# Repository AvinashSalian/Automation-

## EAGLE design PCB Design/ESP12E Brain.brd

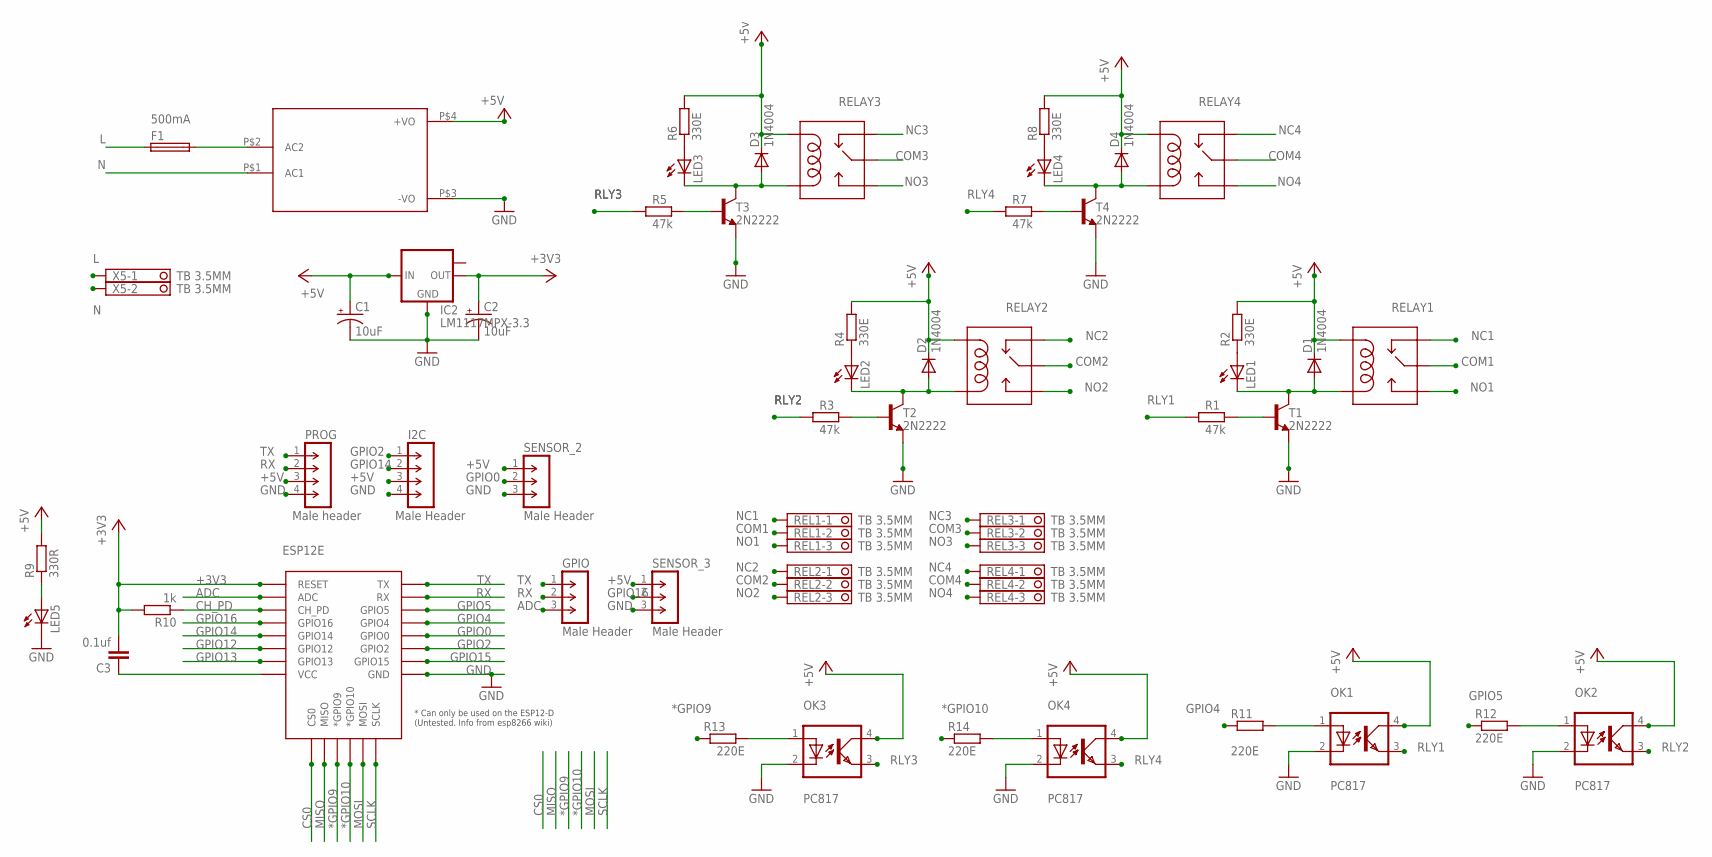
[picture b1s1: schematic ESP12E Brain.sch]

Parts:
C1, C2: 10uF; CPOL-RADIAL-2.5MM-5MM
C3: 0.1uf; C025-030X050
D1, D2, D3, D4: 1N4004; DO41-10
ESP12E: ESP12ESMD; ESP12E-SMD
F1: 500mA; FUSE_HOLDER_5X20MM
GPIO: Male Header; SIP-100-03-32
HLK: HLK-PM013W; HLK-PM01
I2C: Male Header; SIP-100-04-32
IC2: LM1117MPX-3.3; SOT223
LED1, LED2, LED3, LED4, LED5: LEDCHIP-LED0603; CHIP-LED0603
OK1, OK2, OK3, OK4: PC817; DIL04
PROG: Male header; SIP-100-04-32
R1, R3, R5, R7: 47k; 0204/7
R2, R4, R6, R8: 330E; 0204/7
R9: 330R; 0204/7
R10: 1k; 0204/7
R11, R12, R13, R14: 220E; 0204/7
REL1, REL2, REL3, REL4: TB 3.5MM; TERMINAL-BLOCK-3-PIN-3.5MM-ROUND-PAD
RELAY1, RELAY2, RELAY3, RELAY4: SRD-0XVDC-SL-CSRD-05VDC-SL-C; SRD-0XVDC-SL-C
SENSOR_2, SENSOR_3: Male Header; SIP-100-03-32
T1, T2, T3, T4: 2N2222; TO92-EBC-OVAL
X5: TB 3.5MM; TERMINAL-BLOCK-2-PIN-3.5MM-ROUND-PAD

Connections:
*GPIO9: ESP12E.GPIO9 (*GPIO9), R13.1
*GPIO10: ESP12E.GPIO10 (*GPIO10), R14.1
+3V3: C2.1 (+), C3.2, ESP12E.RESET, IC2.2 (OUT), R10.2
+5V: C1.1 (+), D1.C, D2.C, D3.C, D4.C, HLK.P$4 (+VO), I2C.3, IC2.3 (IN), OK1.4 (COL), OK2.4 (COL), OK3.4 (COL), OK4.4 (COL), PROG.3, R2.2, R4.2, R6.2, R8.2, R9.2, RELAY1.COIL1, RELAY2.COIL1, RELAY3.COIL1, RELAY4.COIL1, SENSOR_2.1, SENSOR_3.1
AC2: F1.2, HLK.P$2 (AC2)
ADC: ESP12E.ADC, GPIO.3
CH_PD: ESP12E.CH_PD, R10.1
COM1: REL1.2, RELAY1.SWCOMMON
COM2: REL2.2, RELAY2.SWCOMMON
COM3: REL3.2, RELAY3.SWCOMMON
COM4: REL4.2, RELAY4.SWCOMMON
CS0: ESP12E.CS0
GND: C1.2 (-), C2.2 (-), ESP12E.GND, HLK.P$3 (-VO), I2C.4, IC2.1 (GND), LED5.C, OK1.2 (C), OK2.2 (C), OK3.2 (C), OK4.2 (C), PROG.4, SENSOR_2.3, SENSOR_3.3, T1.E, T2.E, T3.E, T4.E
GPIO0: ESP12E.GPIO0, SENSOR_2.2
GPIO2: ESP12E.GPIO2, I2C.1
GPIO4: ESP12E.GPIO4, R11.1
GPIO5: ESP12E.GPIO5, R12.1
GPIO12: ESP12E.GPIO12
GPIO13: ESP12E.GPIO13
GPIO14: ESP12E.GPIO14, I2C.2
GPIO15: ESP12E.GPIO15
GPIO16: ESP12E.GPIO16, SENSOR_3.2
L: F1.1, X5.1
MISO: ESP12E.MISO
MOSI: ESP12E.MOSI
N: HLK.P$1 (AC1), X5.2
unnamed: R1.2, T1.B
unnamed: D1.A, LED1.C, RELAY1.COIL0, T1.C
unnamed: OK1.1 (A), R11.2
unnamed: D2.A, LED2.C, RELAY2.COIL0, T2.C
unnamed: LED1.A, R2.1
unnamed: R3.2, T2.B
unnamed: LED2.A, R4.1
unnamed: D3.A, LED3.C, RELAY3.COIL0, T3.C
unnamed: OK2.1 (A), R12.2
unnamed: R5.2, T3.B
unnamed: LED3.A, R6.1
unnamed: D4.A, LED4.C, RELAY4.COIL0, T4.C
unnamed: OK3.1 (A), R13.2
unnamed: R7.2, T4.B
unnamed: LED4.A, R8.1
unnamed: C3.1, ESP12E.VCC
unnamed: LED5.A, R9.1
unnamed: OK4.1 (A), R14.2
NC1: REL1.1, RELAY1.SWCLOSED (SWCLOSE)
NC2: REL2.1, RELAY2.SWCLOSED (SWCLOSE)
NC3: REL3.1, RELAY3.SWCLOSED (SWCLOSE)
NC4: REL4.1, RELAY4.SWCLOSED (SWCLOSE)
NO1: REL1.3, RELAY1.SWOPEN
NO2: REL2.3, RELAY2.SWOPEN
NO3: REL3.3, RELAY3.SWOPEN
NO4: REL4.3, RELAY4.SWOPEN
RLY1: OK1.3 (EMIT), R1.1
RLY2: OK2.3 (EMIT), R3.1
RLY3: OK3.3 (EMIT), R5.1
RLY4: OK4.3 (EMIT), R7.1
RX: ESP12E.RXD0 (RX), GPIO.2, PROG.2
SCLK: ESP12E.SCLK
TX: ESP12E.TXD0 (TX), GPIO.1, PROG.1

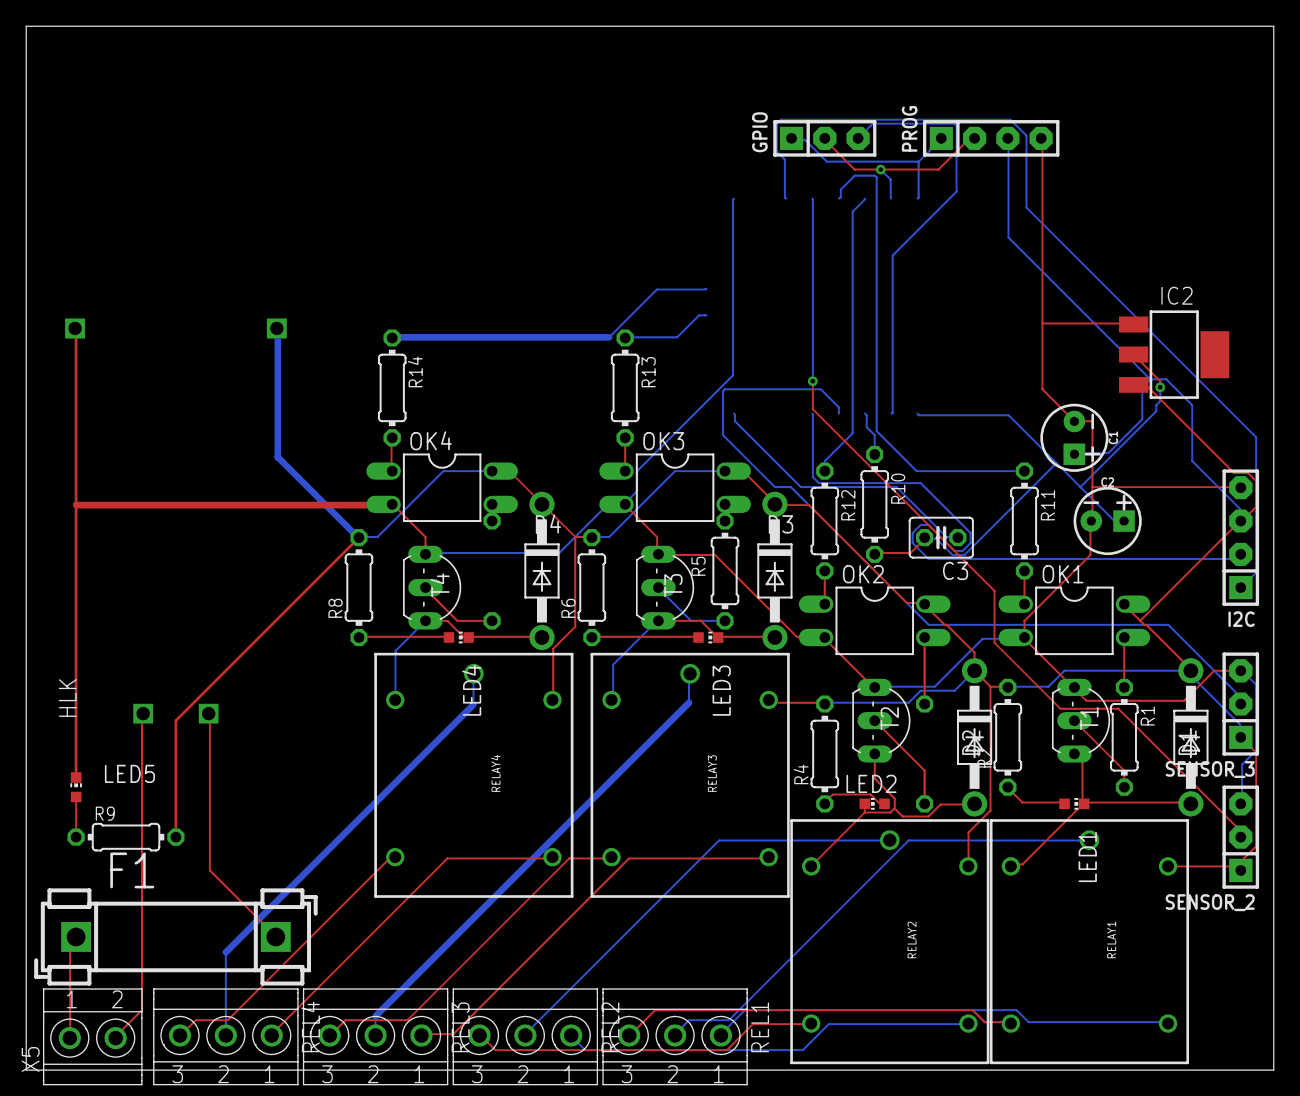
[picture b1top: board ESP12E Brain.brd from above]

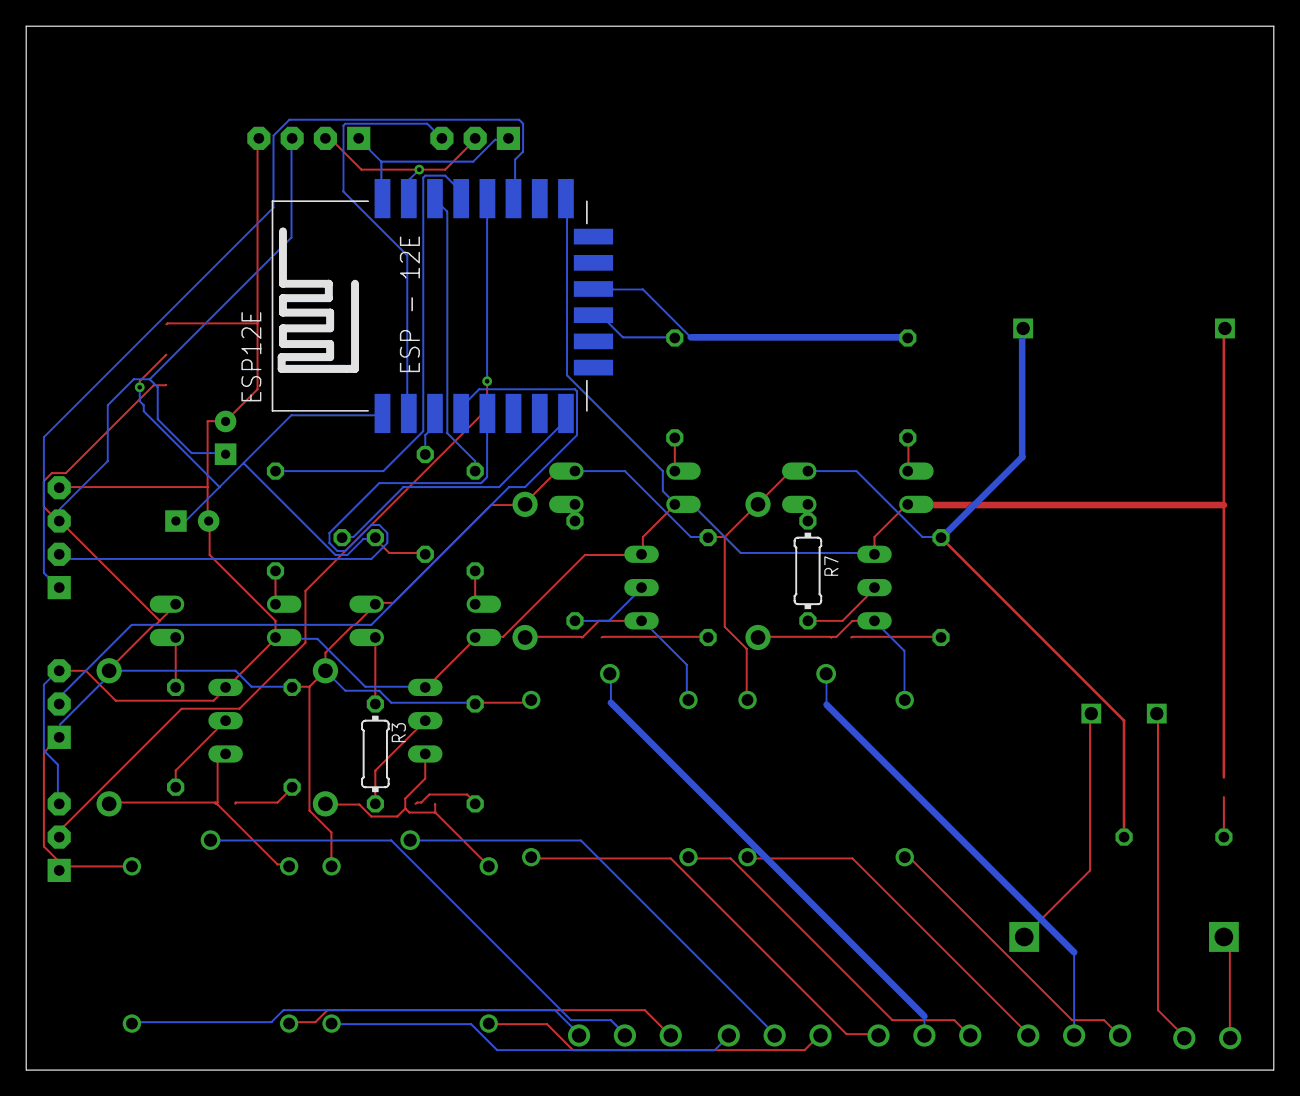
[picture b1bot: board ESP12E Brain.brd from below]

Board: 2 copper layers, 95.2 x 79.7 mm, 52 parts (3 on the bottom side), 52 nets.

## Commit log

2019-03-20 second commit
2019-03-21 Updated brd file

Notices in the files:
parts and their libraries:
SparkFun-Capacitors: Licensing: Creative Commons ShareAlike 4.0 International - https://creativecommons.org/licenses/by-sa/4.0
con-headers-jp: Copyright (C) 2008, Bob Starr
